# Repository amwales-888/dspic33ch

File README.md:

# dspic33ch

Simple development board for 3.3v 80pin TQFP dspic33ch.

- 3.3v LDO powered from 5V USB.
- UART connectivity to USB via ch340 optionally connected using jumpers B1-B2.
- programming interface header.
- With exception of CLKI (B0) and MCLR all other pins are broken out to headers.
- 2 LEDS optionally connected to pins A0-A1 using jumpers.
- 2 Buttons optionally connected to pins A2-A3 using jumpers.

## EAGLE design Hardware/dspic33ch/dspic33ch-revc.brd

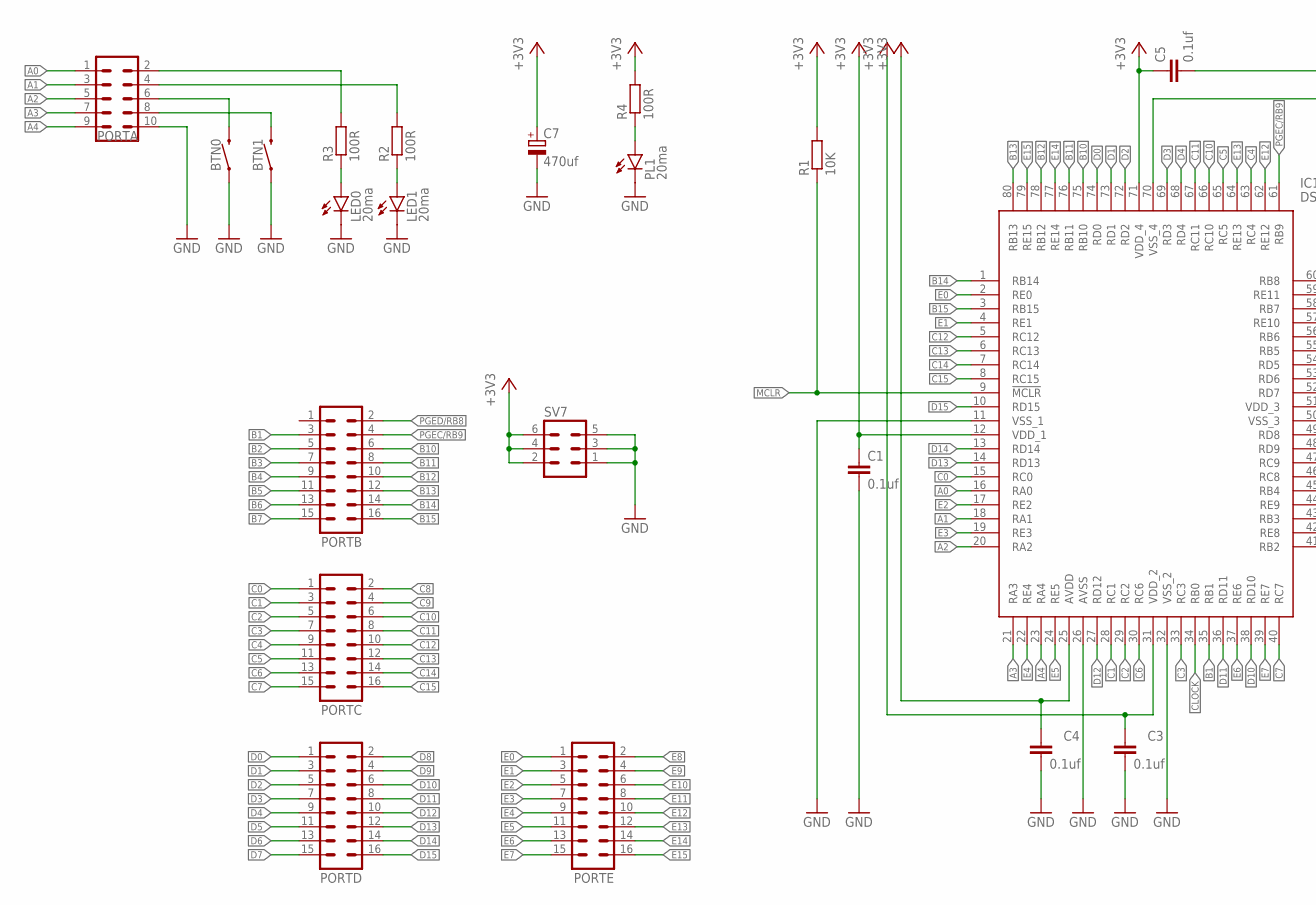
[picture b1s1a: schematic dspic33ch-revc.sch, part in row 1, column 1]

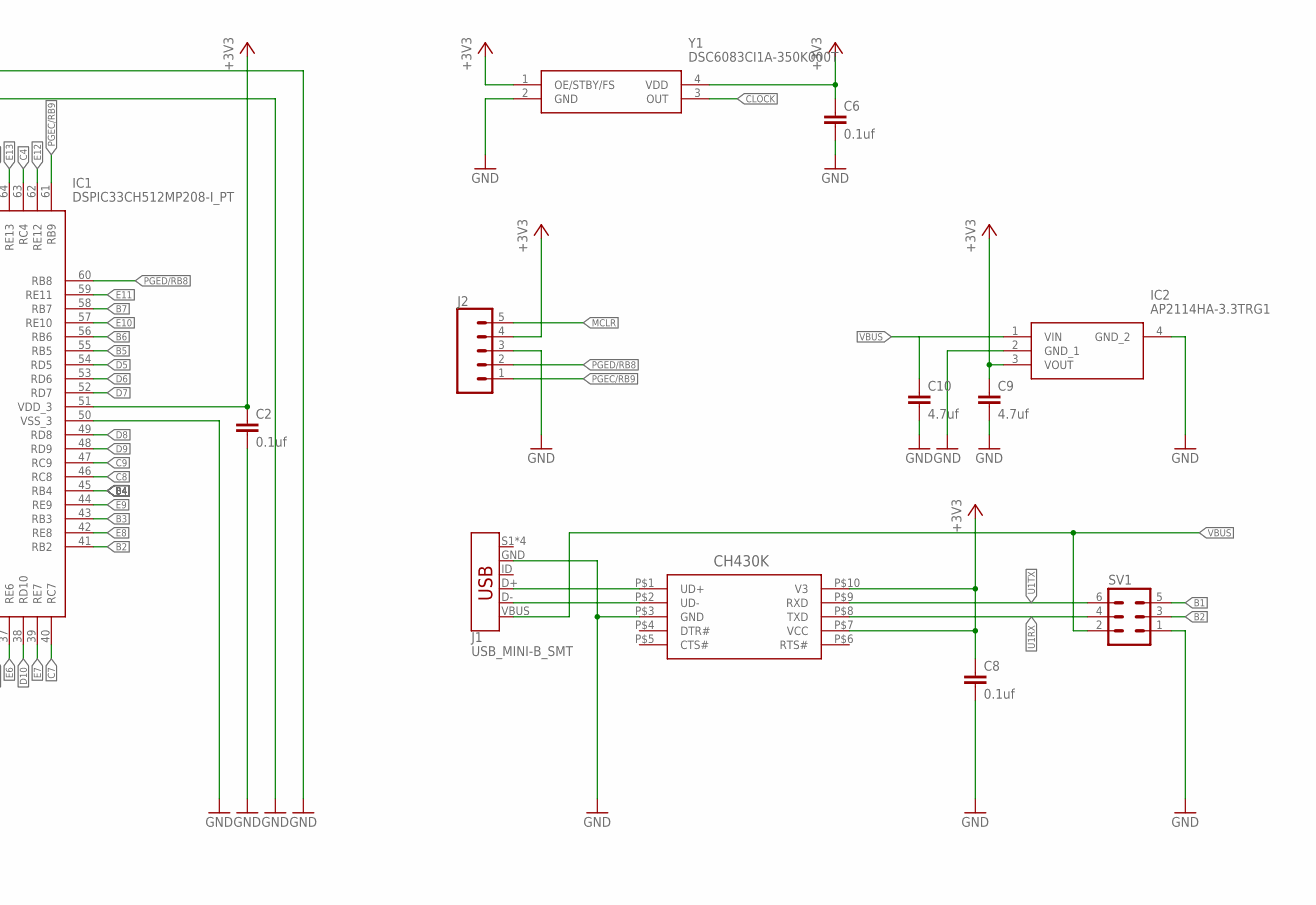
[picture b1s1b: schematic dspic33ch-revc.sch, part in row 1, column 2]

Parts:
BTN0, BTN1: MOMENTARY-SWITCH-SPST-SMD-6.0X3.5MM; TACTILE_SWITCH_SMD_6.0X3.5MM
C1, C2, C3, C4, C5, C6, C8: 0.1uf; C0805
C7: 470uf; E3,5-8
C9, C10: 4.7uf; C0805
IC1: DSPIC33CH512MP208-I_PT; QFP50P1400X1400X120-80N
IC2: AP2114HA-3.3TRG1; SOT230P700X180-4N
J1: USB_MINI-B_SMT; USB-MINIB
J2: CONN_05; 1X05
LED0, LED1: 20ma; SML0805
PL1: 20ma; SML0805
PORTA: MA05-2
PORTB: MA08-2
PORTC: MA08-2
PORTD: MA08-2
PORTE: MA08-2
R1: 10K; R0805
R2, R3, R4: 100R; R0805
SV1, SV7: MA03-2
U$1: CH430K; ESSOP-10
Y1: DSC6083CI1A-350K000T; DSC6083CI1A350K000T

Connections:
+3V3: C1.1, C2.1, C3.1, C4.1, C5.1, C6.1, C7.+, C8.1, C9.1, IC1.12 (VDD_1), IC1.25 (AVDD), IC1.31 (VDD_2), IC1.51 (VDD_3), IC1.71 (VDD_4), IC2.3 (VOUT), J2.4, R1.2, R4.2, SV7.2, SV7.4, SV7.6, U$1.P$7 (VCC), U$1.P$10 (V3), Y1.1 (OE/STBY/FS), Y1.4 (VDD)
A0: IC1.16 (RA0), PORTA.1
A1: IC1.18 (RA1), PORTA.3
A2: IC1.20 (RA2), PORTA.5
A3: IC1.21 (RA3), PORTA.7
A4: IC1.23 (RA4), PORTA.9
B1: IC1.35 (RB1), PORTB.3, SV1.5
B2: IC1.41 (RB2), PORTB.5, SV1.3
B3: IC1.43 (RB3), PORTB.7
B4: IC1.45 (RB4), PORTB.9
B5: IC1.55 (RB5), PORTB.11
B6: IC1.56 (RB6), PORTB.13
B7: IC1.58 (RB7), PORTB.15
B10: IC1.75 (RB10), PORTB.6
B11: IC1.76 (RB11), PORTB.8
B12: IC1.78 (RB12), PORTB.10
B13: IC1.80 (RB13), PORTB.12
B14: IC1.1 (RB14), PORTB.14
B15: IC1.3 (RB15), PORTB.16
C0: IC1.15 (RC0), PORTC.1
C1: IC1.28 (RC1), PORTC.3
C2: IC1.29 (RC2), PORTC.5
C3: IC1.33 (RC3), PORTC.7
C4: IC1.63 (RC4), PORTC.9
C5: IC1.65 (RC5), PORTC.11
C6: IC1.30 (RC6), PORTC.13
C7: IC1.40 (RC7), PORTC.15
C8: IC1.46 (RC8), PORTC.2
C9: IC1.47 (RC9), PORTC.4
C10: IC1.66 (RC10), PORTC.6
C11: IC1.67 (RC11), PORTC.8
C12: IC1.5 (RC12), PORTC.10
C13: IC1.6 (RC13), PORTC.12
C14: IC1.7 (RC14), PORTC.14
C15: IC1.8 (RC15), PORTC.16
CLOCK: IC1.34 (RB0), Y1.3 (OUT)
D0: IC1.74 (RD0), PORTD.1
D1: IC1.73 (RD1), PORTD.3
D2: IC1.72 (RD2), PORTD.5
D3: IC1.69 (RD3), PORTD.7
D4: IC1.68 (RD4), PORTD.9
D5: IC1.54 (RD5), PORTD.11
D6: IC1.53 (RD6), PORTD.13
D7: IC1.52 (RD7), PORTD.15
D8: IC1.49 (RD8), PORTD.2
D9: IC1.48 (RD9), PORTD.4
D10: IC1.38 (RD10), PORTD.6
D11: IC1.36 (RD11), PORTD.8
D12: IC1.27 (RD12), PORTD.10
D13: IC1.14 (RD13), PORTD.12
D14: IC1.13 (RD14), PORTD.14
D15: IC1.10 (RD15), PORTD.16
E0: IC1.2 (RE0), PORTE.1
E1: IC1.4 (RE1), PORTE.3
E2: IC1.17 (RE2), PORTE.5
E3: IC1.19 (RE3), PORTE.7
E4: IC1.22 (RE4), PORTE.9
E5: IC1.24 (RE5), PORTE.11
E6: IC1.37 (RE6), PORTE.13
E7: IC1.39 (RE7), PORTE.15
E8: IC1.42 (RE8), PORTE.2
E9: IC1.44 (RE9), PORTE.4
E10: IC1.57 (RE10), PORTE.6
E11: IC1.59 (RE11), PORTE.8
E12: IC1.62 (RE12), PORTE.10
E13: IC1.64 (RE13), PORTE.12
E14: IC1.77 (RE14), PORTE.14
E15: IC1.79 (RE15), PORTE.16
GND: BTN0.1, BTN1.1, C1.2, C2.2, C3.2, C4.2, C5.2, C6.2, C7.-, C8.2, C9.2, C10.2, IC1.11 (VSS_1), IC1.26 (AVSS), IC1.32 (VSS_2), IC1.50 (VSS_3), IC1.70 (VSS_4), IC2.2 (GND_1), IC2.4 (GND_2), J1.GND, J2.3, LED0.C, LED1.C, PL1.C, PORTA.10, SV1.1, SV7.1, SV7.3, SV7.5, U$1.P$3 (GND), Y1.2 (GND)
MCLR: IC1.9 (!MCLR), J2.5, R1.1
unnamed: LED1.A, R2.1
unnamed: PORTA.2, R3.2
unnamed: PORTA.4, R2.2
unnamed: LED0.A, R3.1
unnamed: BTN0.2, PORTA.6
unnamed: PL1.A, R4.1
unnamed: BTN1.2, PORTA.8
PGEC/RB9: IC1.61 (RB9), J2.1, PORTB.4
PGED/RB8: IC1.60 (RB8), J2.2, PORTB.2
U1RX: SV1.4, U$1.P$8 (TXD)
U1TX: SV1.6, U$1.P$9 (RXD)
USB_N: J1.D-, U$1.P$2 (UD-)
USB_P: J1.D+, U$1.P$1 (UD+)
VBUS: C10.1, IC2.1 (VIN), J1.VBUS, SV1.2

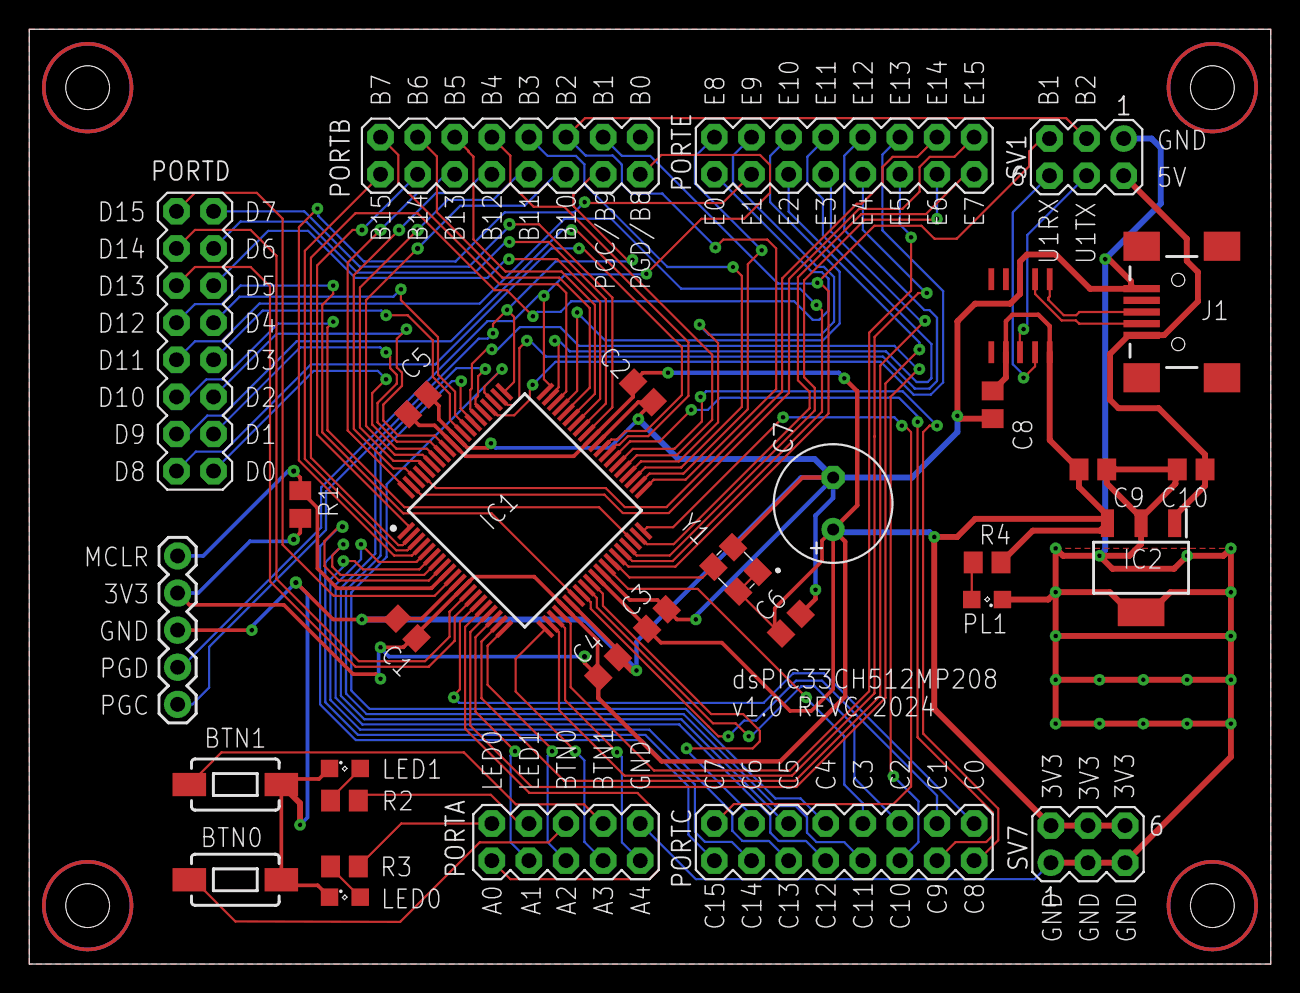
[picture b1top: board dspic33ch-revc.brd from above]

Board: 2 copper layers, 85.0 x 64.0 mm, 32 parts (0 on the bottom side), 84 nets.

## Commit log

2024-07-28 Initial Checkin
2024-07-28 Added Images
2024-07-28 Update README.md
    Added images and introduction
2024-08-04 Fix to ch340 so it operates at 3v3 instead of 5v
2024-08-04 Silkscreen incorrect version
2024-08-31 revc final gerbers produced

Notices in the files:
parts and their libraries:
SparkFun-Connectors: Licensing: Creative Commons ShareAlike 4.0 International - https://creativecommons.org/licenses/by-sa/4.0
